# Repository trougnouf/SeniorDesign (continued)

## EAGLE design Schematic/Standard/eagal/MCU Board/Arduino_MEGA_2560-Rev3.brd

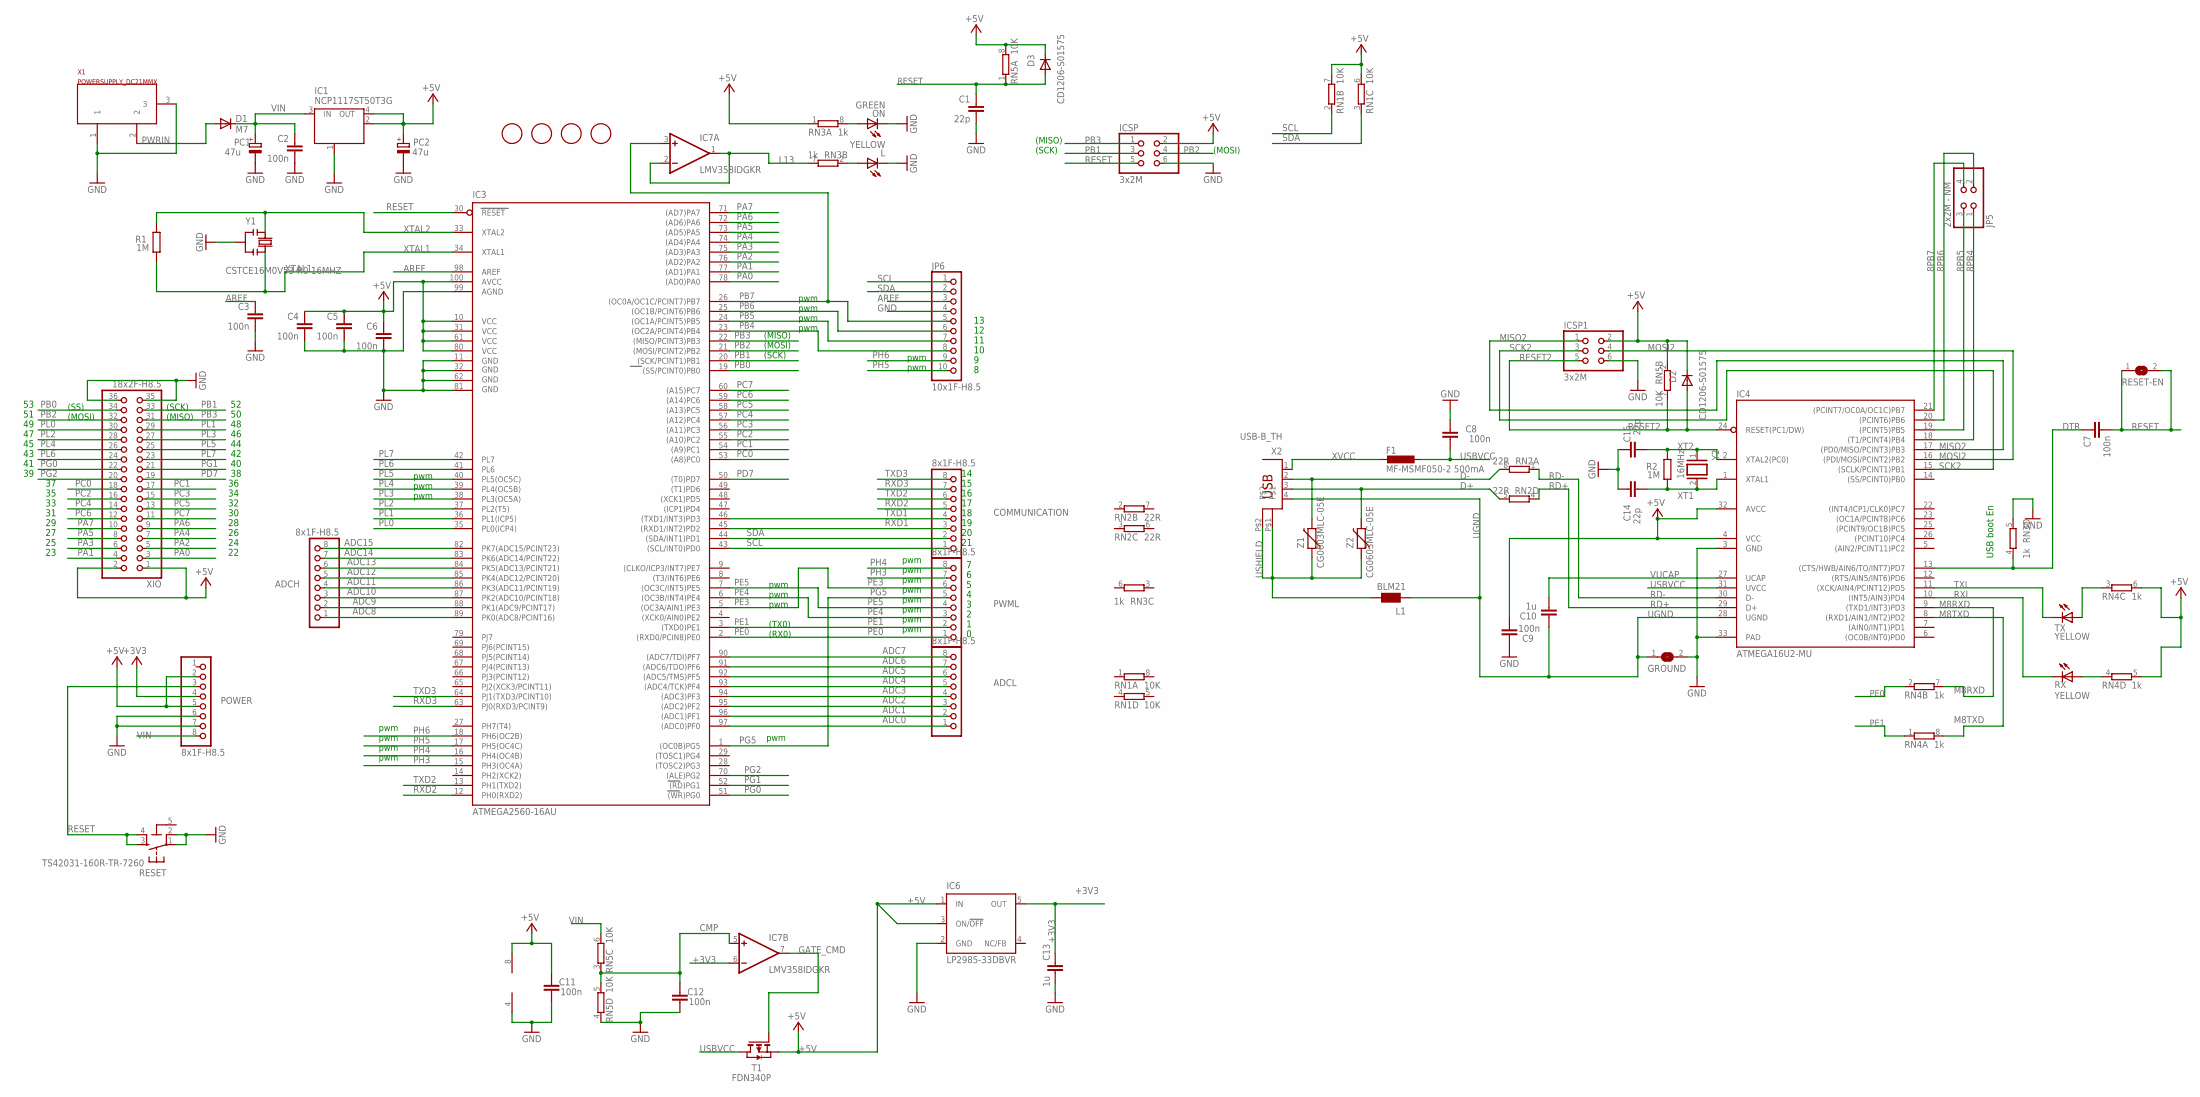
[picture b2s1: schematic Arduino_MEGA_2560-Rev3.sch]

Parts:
ADCH: 8x1F-H8.5; 1X08
ADCL: 8x1F-H8.5; 1X08
C1, C14, C15: 22p; C0603-ROUND
C2, C3, C4, C5, C6, C7, C8, C9, C11, C12: 100n; C0603-ROUND
C10, C13: 1u; C0603-ROUND
COMMUNICATION: 8x1F-H8.5; 1X08
D1: M7; SMB
D2, D3: CD1206-S01575; MINIMELF
F1: MF-MSMF050-2 500mA; L1812
FD1, FD2, FD3, FD4: FIDUCIALMOUNT; FIDUCIA-MOUNT
GROUND: SJ
IC1: NCP1117ST50T3G; SOT223
IC3: ATMEGA2560-16AU; TQFP100
IC4: ATMEGA16U2-MU; MLF32
IC6: LP2985-33DBVR; SOT23-DBV
IC7: LMV358IDGKR; MSOP08
ICSP, ICSP1: 3x2M; 2X03
JP5: 2x2M - NM; 2X02
JP6: 10x1F-H8.5; 1X10
L: YELLOW; CHIP-LED0805
L1: BLM21; 0805
ON: GREEN; CHIP-LED0805
PC1, PC2: 47u; PANASONIC_D
POWER: 8x1F-H8.5; 1X08
PWML: 8x1F-H8.5; 1X08
R1, R2: 1M; R0603-ROUND
RESET: TS42031-160R-TR-7260; TS42
RESET-EN: SJ
RN1, RN5: 10K; CAT16
RN2: 22R; CAY16
RN3, RN4: 1k; CAY16
RX: YELLOW; CHIP-LED0805
T1: FDN340P; SOT-23
TX: YELLOW; CHIP-LED0805
X1: POWERSUPPLY_DC21MMX; POWERSUPPLY_DC-21MM
X2: USB-B_TH; PN61729
XIO: 18x2F-H8.5; 2X18
Y1: CSTCE16M0V53-R0 16MHZ; RESONATOR
Y2: 16MHz; QS
Z1, Z2: CG0603MLC-05E; CT/CN0603

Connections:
5-GND: RESET.5 (5-GND)
8PB4: IC4.18 ((T1/PCINT4)PB4), JP5.1
8PB5: IC4.19 ((PCINT5)PB5), JP5.3
8PB6: IC4.20 ((PCINT6)PB6), JP5.2
8PB7: IC4.21 ((PCINT7/OC0A/OC1C)PB7), JP5.4
+3V3: C13.2, IC6.5 (OUT), IC7.6 (-IN), POWER.4
+5V: C4.1, C5.1, C6.1, C9.1, C11.2, D2.C, D3.C, IC1.2 (OUT), IC1.4 (OUT), IC3.10 (VCC), IC3.31 (VCC1), IC3.61 (VCC2), IC3.80 (VCC3), IC3.100 (AVCC), IC4.4 (VCC), IC4.32 (AVCC), IC6.1 (IN), IC6.3 (ON/!OFF), IC7.8 (V+), ICSP.2, ICSP1.2, PC2.+, POWER.2, POWER.5, RN1.6 (2), RN1.7 (2), RN3.1, RN4.5 (2), RN4.6 (2), RN5.2 (1), RN5.8 (2), T1.2 (S), XIO.1, XIO.2
ADC0: ADCL.1, IC3.97 ((ADC0)PF0)
ADC1: ADCL.2, IC3.96 ((ADC1)PF1)
ADC2: ADCL.3, IC3.95 ((ADC2)PF2)
ADC3: ADCL.4, IC3.94 ((ADC3)PF3)
ADC4: ADCL.5, IC3.93 ((ADC4/TCK)PF4)
ADC5: ADCL.6, IC3.92 ((ADC5/TMS)PF5)
ADC6: ADCL.7, IC3.91 ((ADC6/TDO)PF6)
ADC7: ADCL.8, IC3.90 ((ADC7/TDI)PF7)
ADC8: ADCH.1, IC3.89 (PK0(ADC8/PCINT16))
ADC9: ADCH.2, IC3.88 (PK1(ADC9/PCINT17))
ADC10: ADCH.3, IC3.87 (PK2(ADC10/PCINT18))
ADC11: ADCH.4, IC3.86 (PK3(ADC11/PCINT19))
ADC12: ADCH.5, IC3.85 (PK4(ADC12/PCINT20))
ADC13: ADCH.6, IC3.84 (PK5(ADC13/PCINT21))
ADC14: ADCH.7, IC3.83 (PK6(ADC14/PCINT22))
ADC15: ADCH.8, IC3.82 (PK7(ADC15/PCINT23))
AREF: C3.1, IC3.98 (AREF), JP6.3
CMP: C12.2, IC7.5 (+IN), RN5.3 (1), RN5.5 (2)
D+: RN2.5 (2), X2.3, Z2.2
D-: RN2.8 (2), X2.2, Z1.2
DTR: C7.1, IC4.13 ((CTS/HWB/AIN6/TO/INT7)PD7), RN3.4 (1)
GATE_CMD: IC7.7 (OUT), T1.3 (G)
GND: C1.2, C2.2, C3.2, C4.2, C5.2, C6.2, C8.2, C9.2, C11.1, C12.1, C13.1, C14.2, C15.2, GROUND.2, IC1.1 (GND/ADJ), IC3.11 (GND), IC3.32 (GND1), IC3.62 (GND2), IC3.81 (GND3), IC3.99 (AGND), IC4.3 (GND), IC4.33 (PAD), IC6.2 (GND), IC7.4 (V-), ICSP.6, ICSP1.6, JP6.4, L.C, ON.C, PC1.-, PC2.-, POWER.6, POWER.7, RESET.1, RESET.2, RN3.5 (2), RN5.4 (1), X1.1, X1.3, XIO.35, XIO.36, Y1.2
L13: IC7.1 (OUT), IC7.2 (-IN), RN3.7 (2)
M8RXD: IC4.9 ((TXD1/INT3)PD3), RN4.7 (2)
M8TXD: IC4.8 ((RXD1/AIN1/INT2)PD2), RN4.8 (2)
MISO2: IC4.17 ((PD0/MISO/PCINT3)PB3), ICSP1.1
MOSI2: IC4.16 ((PDI/MOSI/PCINT2)PB2), ICSP1.4
unnamed: L.A, RN3.2 (1)
unnamed: ON.A, RN3.8 (2)
unnamed: RN4.4 (1), RX.A
unnamed: RN4.3 (1), TX.A
PA0: IC3.78 ((AD0)PA0), XIO.3
PA1: IC3.77 ((AD1)PA1), XIO.4
PA2: IC3.76 ((AD2)PA2), XIO.5
PA3: IC3.75 ((AD3)PA3), XIO.6
PA4: IC3.74 ((AD4)PA4), XIO.7
PA5: IC3.73 ((AD5)PA5), XIO.8
PA6: IC3.72 ((AD6)PA6), XIO.9
PA7: IC3.71 ((AD7)PA7), XIO.10
PB0: IC3.19 ((SS/PCINT0)PB0), XIO.34
PB1: IC3.20 ((SCK/PCINT1)PB1), ICSP.3, XIO.33
PB2: IC3.21 ((MOSI/PCINT2)PB2), ICSP.4, XIO.32
PB3: IC3.22 ((MISO/PCINT3)PB3), ICSP.1, XIO.31
PB4: IC3.23 ((OC2A/PCINT4)PB4), JP6.8
PB5: IC3.24 ((OC1A/PCINT5)PB5), JP6.7
PB6: IC3.25 ((OC1B/PCINT6)PB6), JP6.6
PB7: IC3.26 ((OC0A/OC1C/PCINT7)PB7), IC7.3 (+IN), JP6.5
PC0: IC3.53 ((A8)PC0), XIO.18
PC1: IC3.54 ((A9)PC1), XIO.17
PC2: IC3.55 ((A10)PC2), XIO.16
PC3: IC3.56 ((A11)PC3), XIO.15
PC4: IC3.57 ((A12)PC4), XIO.14
PC5: IC3.58 ((A13)PC5), XIO.13
PC6: IC3.59 ((A14)PC6), XIO.12
PC7: IC3.60 ((A15)PC7), XIO.11
PD7: IC3.50 ((T0)PD7), XIO.19
PE0: IC3.2 ((RXD0/PCIN8)PE0), PWML.1, RN4.2 (1)
PE1: IC3.3 ((TXD0)PE1), PWML.2, RN4.1
PE3: IC3.5 ((OC3A/AIN1)PE3), PWML.6
PE4: IC3.6 ((OC3B/INT4)PE4), PWML.3
PE5: IC3.7 ((OC3C/INT5)PE5), PWML.4
PG0: IC3.51 ((WR)PG0), XIO.22
PG1: IC3.52 ((RD)PG1), XIO.21
PG2: IC3.70 ((ALE)PG2), XIO.20
PG5: IC3.1 ((OC0B)PG5), PWML.5
PH3: IC3.15 (PH3(OC4A)), PWML.7
PH4: IC3.16 (PH4(OC4B)), PWML.8
PH5: IC3.17 (PH5(OC4C)), JP6.10
PH6: IC3.18 (PH6(OC2B)), JP6.9
PL0: IC3.35 (PL0(ICP4)), XIO.30
PL1: IC3.36 (PL1(ICP5)), XIO.29
PL2: IC3.37 (PL2(T5)), XIO.28
PL3: IC3.38 (PL3(OC5A)), XIO.27
PL4: IC3.39 (PL4(OC5B)), XIO.26
PL5: IC3.40 (PL5(OC5C)), XIO.25
PL6: IC3.41 (PL6), XIO.24
PL7: IC3.42 (PL7), XIO.23
PWRIN: D1.A, X1.2
RD+: IC4.29 (D+), RN2.4 (1)
RD-: IC4.30 (D-), RN2.1
RESET: C1.1, C7.2, D3.A, IC3.30 (RESET), ICSP.5, POWER.3, RESET.3, RESET.4, RESET-EN.1, RESET-EN.2, RN5.1
RESET2: D2.A, IC4.24 (RESET(PC1/DW)), ICSP1.5, RN5.7 (2)
RXD1: COMMUNICATION.3, IC3.45 ((RXD1/INT2)PD2)
RXD2: COMMUNICATION.5, IC3.12 (PH0(RXD2))
RXD3: COMMUNICATION.7, IC3.63 (PJ0(RXD3/PCINT9))
RXL: IC4.10 ((INT5/AIN3)PD4), RX.C
SCK2: IC4.15 ((SCLK/PCINT1)PB1), ICSP1.3
SCL: COMMUNICATION.1, IC3.43 ((SCL/INT0)PD0), JP6.1, RN1.2 (1)
SDA: COMMUNICATION.2, IC3.44 ((SDA/INT1)PD1), JP6.2, RN1.3 (1)
TXD1: COMMUNICATION.4, IC3.46 ((TXD1/INT3)PD3)
TXD2: COMMUNICATION.6, IC3.13 (PH1(TXD2))
TXD3: COMMUNICATION.8, IC3.64 (PJ1(TXD3/PCINT10))
TXL: IC4.11 ((XCK/AIN4/PCINT12)PD5), TX.C
UGND: C10.2, GROUND.1, IC4.28 (UGND), L1.1, X2.4
USBVCC: C8.1, F1.1, IC4.31 (UVCC), T1.1 (D)
USHIELD: L1.2, X2.P$1, X2.P$2, Z1.1, Z2.1
VIN: C2.1, D1.C, IC1.3 (IN), PC1.+, POWER.8, RN5.6 (2)
VUCAP: C10.1, IC4.27 (UCAP)
XT1: C14.1, IC4.1 (XTAL1), R2.1, Y2.2
XT2: C15.1, IC4.2 (XTAL2(PC0)), R2.2, Y2.1
XTAL1: IC3.34 (XTAL1), R1.1, Y1.3
XTAL2: IC3.33 (XTAL2), R1.2, Y1.1
XVCC: F1.2, X2.1

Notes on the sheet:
(SCK)
(MISO)
(MOSI)
pwm
(TX0)
(RX0)
(SS)
USB boot En

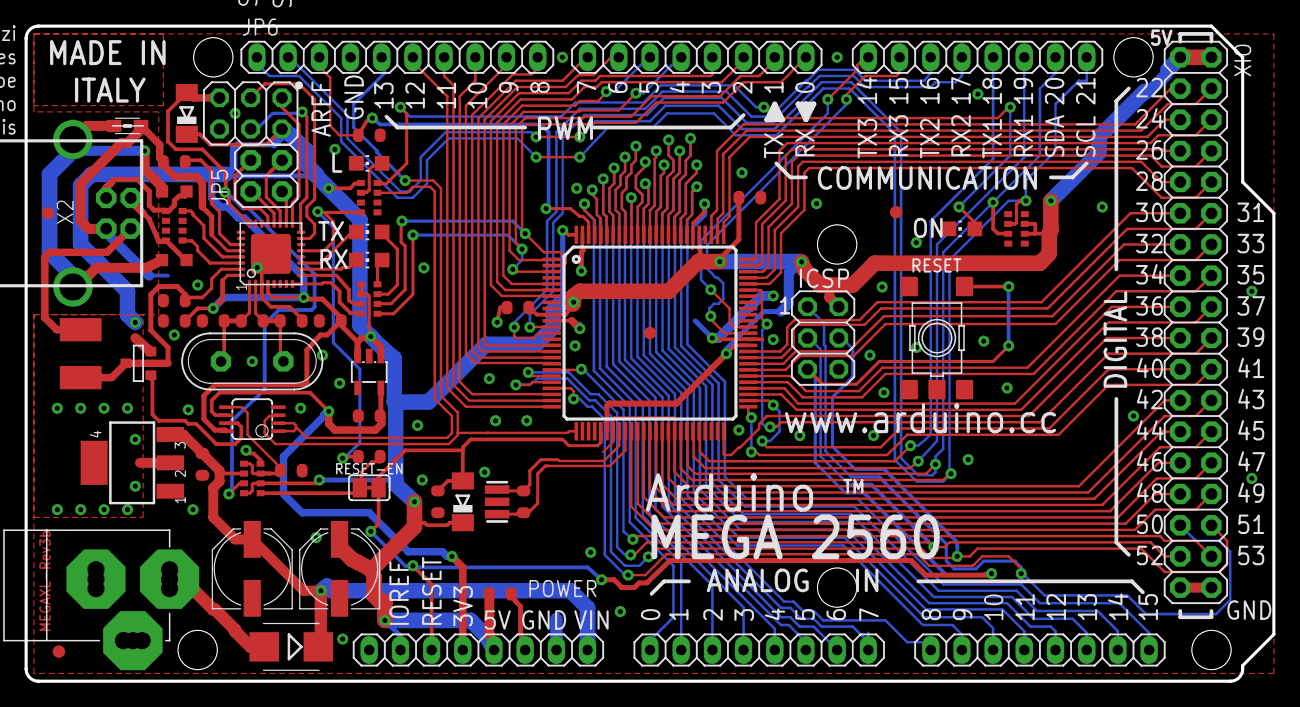
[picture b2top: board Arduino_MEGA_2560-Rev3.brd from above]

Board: 2 copper layers, 101.6 x 53.3 mm, 62 parts (1 on the bottom side), 110 nets.

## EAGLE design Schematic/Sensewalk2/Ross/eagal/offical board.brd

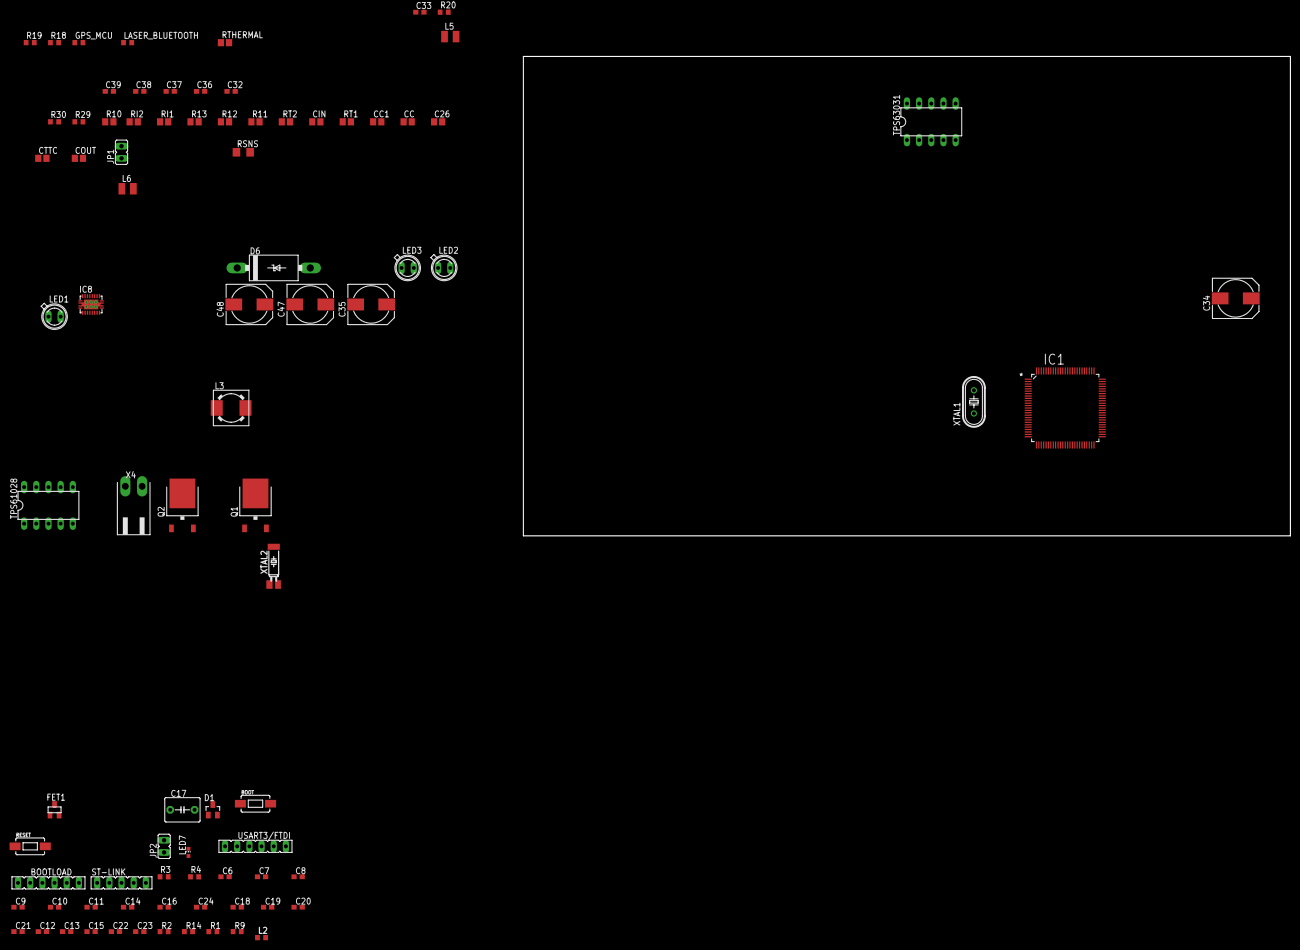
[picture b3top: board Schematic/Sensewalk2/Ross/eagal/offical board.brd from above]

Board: 2 copper layers, 160.0 x 100.0 mm, 85 parts (0 on the bottom side), 49 nets, no tracks yet.

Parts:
BOOT: SWITCH-MOMENTARY-2-SMD-1101NE; TACTILE-SWITCH-1101NE
BOOTLOAD: FE06
C6, C7, C8, C9, C10, C11, C14, C16, C24: 100nF; C0603
C12, C13, C15: 1uF; C0603
C17: 0.22F; C5B5
C18, C19: 6.8pF; C0603
C20: 22pF; C0603
C21: 22pf; C0603
C22, C23: 2u2; C0603
C26: 0.1uF; C0805
C32: 2.2uF; C0603
C33: C0603
C34, C47, C48: 347uF; 150CLZ-0810
C35: 150CLZ-0810
C36, C37, C38, C39: 10uF; C0603
CC, CC1: 0.1uF; C0805
CIN: 10uF; C0805
COUT: 10uF; C0805
CTTC: 0.1uF; C0805
D1: BAT54; SOT23
D6: MMBZ18VALT1; C4111-15
FET1: DMP2160UW; SUPER-SOT3
GPS_MCU: R0603
IC1: STM32F746VGT6; QFP50P1600X1600X160-100N
IC8: BQ24123; QFN20_3,5X4,5
JP1, JP2: JP1
L2: RCL_L0603
L3: 10uH; DR73
L5: L2825P
L6: 1.5uH; L2825P
LASER_BLUETOOTH: R0603
LED1, LED2, LED3: SFH482
LED7: CHIP-LED0603
Q1, Q2: FDD4141TO252; TO252
R1, R9, R14: 10K; R0603
R2: 47R; R0603
R3: 100R; R0603
R4: 270R; R0603
R10: 10k; R0805
R11, R12, R13: 1.5k; R0805
R18, R19, R20: R0603
R29, R30: 100k; R0603
RESET: SWITCH-MOMENTARY-2-SMD-1101NE; TACTILE-SWITCH-1101NE
RI1, RI2: 7.5k; R0805
RSNS: 0.1; R1206
RT1: 9.31k; R0805
RT2: 442k; R0805
RTHERMAL: R0805
ST-LINK: FE05-1
TPS61028, TPS63031: DIL10
USART3/FTDI: FE06
X4: 90-2
XTAL1: 8MHz; HC49U-V
XTAL2: 32768Hz; CRYSTAL_TC26H_3_REPAIR_SMD_SMALL_PITCH

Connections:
+5V: BOOTLOAD.3, C32.1, C34.+, C38.1, C39.1, C47.+, C48.+, GPS_MCU.2, JP2.1, LASER_BLUETOOTH.2, Q1.1, Q1.3, Q2.1, Q2.3, R18.2, R29.2, R30.2, TPS61028.2, TPS63031.1, TPS63031.10, USART3/FTDI.3
AGND: C32.2, C33.2, C34.-, C35.-, C36.2, C37.2, C38.2, C39.2, C47.-, C48.-, GPS_MCU.1, LASER_BLUETOOTH.1, R20.1, R29.1, R30.1, TPS61028.5, TPS61028.8, TPS61028.10, TPS63031.3, TPS63031.9
BOOT0: BOOT.P$1, FET1.3, IC1.94, R1.2
GND: BOOTLOAD.1, C6.2, C7.2, C8.2, C9.2, C10.2, C11.2, C12.2, C13.2, C14.2, C15.2, C16.2, C17.2, C18.2, C19.2, C20.2, C21.2, C22.2, C23.2, C24.2, C26.2, CC.2, CC1.2, CIN.2, COUT.2, CTTC.2, D6.A, IC1.10, IC1.19, IC1.26, IC1.49, IC1.74, IC1.99, IC8.10, IC8.16, IC8.17, IC8.18, R1.1, R4.1, R14.1, RESET.P$1, RI1.2, RI2.2, RT2.1, RTHERMAL.2, ST-LINK.3, USART3/FTDI.1, X4.2, XTAL2.GND
unnamed: Q1.2, Q2.2
unnamed: D6.C, IC8.1, IC8.20, L3.1
unnamed: CC.1, COUT.1, IC8.15, L3.2, RSNS.1
unnamed: IC8.8, RI1.1
unnamed: IC8.9, RI2.1
unnamed: IC8.12, RT1.1, RT2.2, RTHERMAL.1
unnamed: CC1.1, IC8.11, RT1.2
unnamed: LED3.A, R13.1
unnamed: LED2.A, R12.1
unnamed: LED1.A, R11.1
unnamed: IC8.2, LED1.K
unnamed: IC8.19, LED2.K
unnamed: IC8.5, LED3.K
unnamed: CTTC.1, IC8.7
unnamed: IC8.13, R10.1
unnamed: C26.1, CIN.1, IC8.3, IC8.4, IC8.6, JP1.2, R10.2, R11.2, R12.2, R13.2
unnamed: D1.3, R3.2
unnamed: R18.1, TPS61028.4
unnamed: R19.2, TPS61028.1, TPS61028.6
unnamed: L5.1, TPS61028.9
unnamed: C33.1, C35.+, C36.1, IC8.14, L5.2, R19.1, R20.2, RSNS.2, TPS61028.7, TPS63031.5, X4.1
unnamed: L6.2, TPS63031.2
unnamed: L6.1, TPS63031.4
unnamed: C37.1, TPS63031.6, TPS63031.7, TPS63031.8
unnamed: LED7.C, R4.2
NRST: C24.1, IC1.14, R9.1, RESET.P$2, ST-LINK.5
PA9: BOOTLOAD.5, IC1.68
PA10: BOOTLOAD.4, IC1.69
PA13: IC1.72, ST-LINK.4
PA14: IC1.76, ST-LINK.2
PB2: IC1.36, R14.2
PC13: IC1.7, LED7.A
PC14: C18.1, IC1.8, XTAL2.1
PC15: C19.1, IC1.9, XTAL2.2
PD1: FET1.1, IC1.82
PD8: IC1.55, USART3/FTDI.5
PD9: IC1.56, USART3/FTDI.4
PH0: C21.1, IC1.12, XTAL1.2
PH1: C20.1, IC1.13, XTAL1.1
VBAT: C17.1, IC1.6, R3.1
VCAP_1: C22.1, IC1.48
VCAP_2: C23.1, IC1.73
VCC: BOOT.P$2, C6.1, C7.1, C8.1, C9.1, C10.1, C11.1, C12.1, D1.1, FET1.2, IC1.11, IC1.27, IC1.50, IC1.75, IC1.100, L2.1, R9.2, ST-LINK.1
VDDA: C13.1, C14.1, IC1.21, L2.2, R2.2
VREF: C15.1, C16.1, IC1.20, R2.1

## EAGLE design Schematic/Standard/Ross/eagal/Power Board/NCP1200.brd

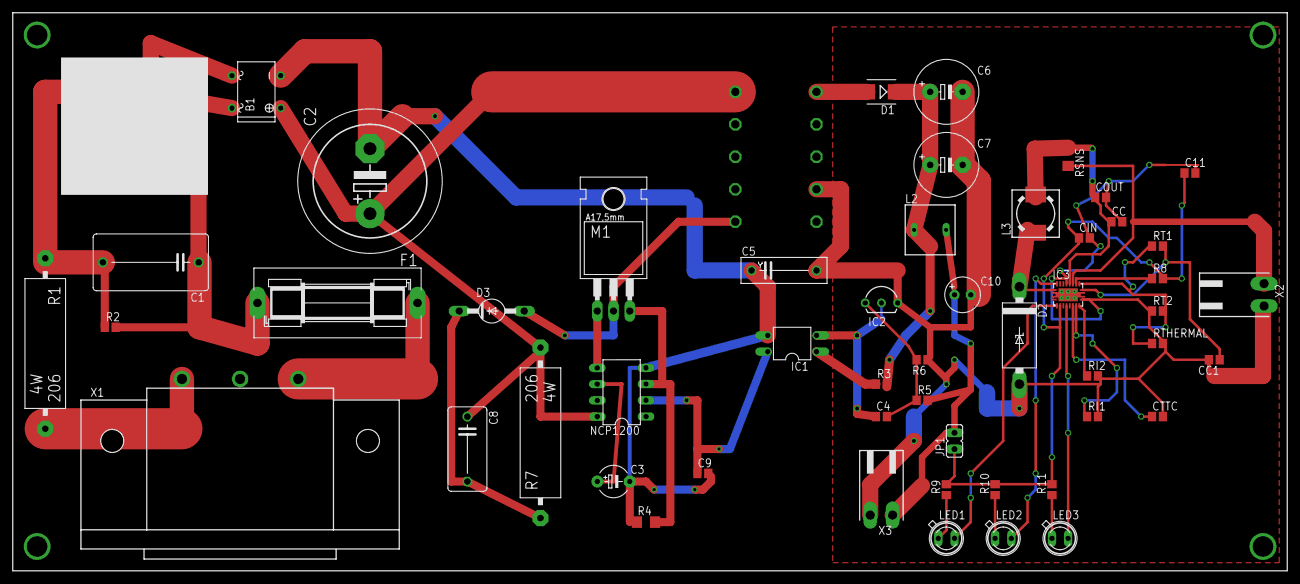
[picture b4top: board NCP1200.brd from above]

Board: 2 copper layers, 199.4 x 87.3 mm, 54 parts (1 on the bottom side), 37 nets.

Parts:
B1: B-DIL
C1: 1uF; C150-091X182
C2: 47uF; EB22,5D
C3: 22uF; E5-5
C4: 100nF; C0805
C5: 2.2nF; YC10B4
C6, C7: 470uF; E5-10,5
C8: 10nF; C102-064X133
C9: 1nF; C0805
C10: 100uF; E2,5-6
C11: 0.1uF; C0805
CC, CC1: 0.1uF; C0805
CIN: 10uF; C0805
COUT: 10uF; C0805
CTTC: 0.1uF; C0805
D1: MBR360T3; SMB
D2: MMBZ18VALT1; C4111-15
D3: MUR160; SGA-10
F1: SH25
IC1: PC817; DIL04
IC2: TL431; LP_O-PBCY-W3
IC3: BQ24123; QFN20_3,5X4,5
JP1: JP1
L2: 22uH; SD8
L3: 10uH; DR73
LED1, LED2, LED3: SFH482
M1: NDF03N60ZG; TO220
NCP1200: DIL08
R1: 10; KH206-8
R2: 1Meg; R0805
R3: 560; R0805
R4: 1.8; R1206
R5: 3.9k; R0805
R6: 1k; R0805
R7: 22k; KH206-8
R8: 10k; R0805
R9, R10, R11: 1.5k; R0805
RI1, RI2: 7.5k; R0805
RSNS: 0.1; R1206
RT1: 9.31k; R0805
RT2: 442k; R0805
RTHERMAL: R0805
U$1: RENCO1
U$2: L1CHO5; L1CHO
X1: 6ESRM-P
X2, X3: 90-2

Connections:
GND: C5.2, C6.-, C7.-, C10.-, C11.2, CC.2, CC1.2, CIN.2, COUT.2, CTTC.2, D2.A, IC2.3, IC3.10, IC3.16, IC3.17, IC3.18, R6.1, RI1.2, RI2.2, RT2.1, RTHERMAL.2, U$1.P7, X2.2, X3.2
unnamed: D2.C, IC3.1, IC3.20, L3.1
unnamed: C1.2, R1.1, R2.1, U$2.P3
unnamed: CC.1, COUT.1, IC3.15, L3.2, RSNS.1
unnamed: B1.AC1, U$2.P2
unnamed: B1.AC2, U$2.P4
unnamed: IC3.8, RI1.1
unnamed: B1.+, C2.+, C8.1, NCP1200.8, R7.2, U$1.P1
unnamed: C9.1, IC1.4, NCP1200.2
unnamed: M1.1, NCP1200.5
unnamed: M1.3, NCP1200.3, R4.2
unnamed: C3.+, NCP1200.6
unnamed: C11.1, CIN.1, IC3.3, IC3.4, IC3.6, JP1.1, R8.2, R9.2, R10.2, R11.2
unnamed: D1.A, U$1.P10
unnamed: C8.2, D3.C, R7.1
unnamed: D3.A, M1.2, U$1.P5
unnamed: C6.+, C7.+, D1.C, L2.1, R3.2
unnamed: IC1.1, R3.1
unnamed: IC3.9, RI2.1
unnamed: C4.2, IC2.1, R5.1, R6.2
unnamed: C4.1, IC1.2, IC2.2
unnamed: IC3.12, RT1.1, RT2.2, RTHERMAL.1
unnamed: CC1.1, IC3.11, RT1.2
unnamed: LED3.A, R11.1
unnamed: LED2.A, R10.1
unnamed: LED1.A, R9.1
unnamed: IC3.2, LED1.K
unnamed: IC3.19, LED2.K
unnamed: IC3.5, LED3.K
unnamed: CTTC.1, IC3.7
unnamed: IC3.13, R8.1
unnamed: C1.1, F1.2, R2.2, U$2.P1
unnamed: R1.2, X1.1
unnamed: IC3.14, RSNS.2, X2.1
unnamed: F1.1, X1.3
unnamed: C10.+, JP1.2, L2.2, R5.2, X3.1
PE: B1.-, C2.-, C3.-, C5.1, C9.2, IC1.3, NCP1200.4, R4.1

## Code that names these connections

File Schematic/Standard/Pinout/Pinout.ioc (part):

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Mcu.Name=STM32F746Z(E-G)Tx
Mcu.Package=LQFP144
Mcu.UserName=STM32F746ZGTx
PA0/WKUP.GPIOParameters=GPIO_Label
PA0/WKUP.GPIO_Label=UART_TX_Laser
PA0/WKUP.Mode=Asynchronous
PA0/WKUP.Signal=UART4_TX
PA1.GPIOParameters=GPIO_Label
PA1.GPIO_Label=UART_RX_Laser
PA1.Mode=Asynchronous
PA1.Signal=UART4_RX
PA10.Mode=Slave_8_bits_External_Synchro
PA10.Signal=DCMI_D1
PA13.Mode=Trace-Asynchronous_SW
PA13.Signal=SYS_JTMS-SWDIO
PA14.Mode=Trace-Asynchronous_SW
PA14.Signal=SYS_JTCK-SWCLK
PA15.GPIOParameters=GPIO_Label
PA15.GPIO_Label=SPI1_NSS_Compass
PA15.Mode=NSS_Signal_Hard_Input
PA15.Signal=SPI1_NSS
PA2.GPIOParameters=GPIO_Label
PA2.GPIO_Label=ADC_IN2_Mic
PA2.Signal=ADCx_IN2
PA4.Mode=Slave_8_bits_External_Synchro
PA4.Signal=DCMI_HSYNC
PA5.GPIOParameters=GPIO_Label
PA5.GPIO_Label=SPI_CLK_Compass
PA5.Mode=Full_Duplex_Master
PA5.Signal=SPI1_SCK
PA6.Mode=Slave_8_bits_External_Synchro
PA6.Signal=DCMI_PIXCLK
PA7.GPIOParameters=GPIO_Label
PA7.GPIO_Label=SPI_MOSI_Compass
PA7.Mode=Full_Duplex_Master
PA7.Signal=SPI1_MOSI
PA9.GPIOParameters=GPIO_Label
PA9.GPIO_Label=USART1_TX_Debug
PA9.Mode=Asynchronous
PA9.Signal=USART1_TX
PB10.GPIOParameters=GPIO_Label
PB10.GPIO_Label=I2C2_SCL_Codec
PB10.Mode=I2C
PB10.Signal=I2C2_SCL
PB11.GPIOParameters=GPIO_Label
PB11.GPIO_Label=I2C2_SDA_Codec
PB11.Mode=I2C
PB11.Signal=I2C2_SDA
PB12.GPIOParameters=GPIO_Label
PB12.GPIO_Label=DATA_REQ_Codec
PB12.Signal=GPIO_Input
PB13.Mode=TX_Only_Simplex_Unidirect_Master
PB13.Signal=SPI2_SCK
PB14.GPIOParameters=GPIO_Label
PB14.GPIO_Label=RST_Codec
PB14.Signal=GPIO_Output
PB2.Mode=Single Bank 1
PB2.Signal=QUADSPI_CLK
PB3.Mode=Trace-Asynchronous_SW
PB3.Signal=SYS_JTDO-SWO
PB4.GPIOParameters=GPIO_Label
PB4.GPIO_Label=SPI_MISO_Compass
PB4.Mode=Full_Duplex_Master
PB4.Signal=SPI1_MISO
PB6.Mode=Single Bank 1
PB6.Signal=QUADSPI_BK1_NCS
PB7.GPIOParameters=GPIO_Label
PB7.GPIO_Label=USART1_RX_Debug
PB7.Mode=Asynchronous
PB7.Signal=USART1_RX
PC0.Signal=FMC_SDNWE
PC1.Mode=TX_Only_Simplex_Unidirect_Master
PC1.Signal=SPI2_MOSI
PC12.Mode=SD_1_bit
PC12.Signal=SDMMC1_CK
PC13.GPIOParameters=GPIO_Label
PC13.GPIO_Label=RET_Camera
PC13.Signal=GPIO_Output
PC2.Mode=SdramChipSelect1_1
PC2.Signal=FMC_SDNE0
PC3.Mode=SdramChipSelect1_1
PC3.Signal=FMC_SDCKE0
PC4.GPIOParameters=GPIO_Label
PC4.GPIO_Label=INT_Compass
PC4.Signal=GPIO_Output
PC5.GPIOParameters=GPIO_Label
PC5.GPIO_Label=TRIG_Compass
PC5.Signal=GPIO_Output
PC6.Mode=Slave_8_bits_External_Synchro
PC6.Signal=DCMI_D0
PC7.GPIOParameters=GPIO_Label
PC7.GPIO_Label=USART6_RX_BT
PC7.Mode=Asynchronous
PC7.Signal=USART6_RX
PC8.Mode=SD_1_bit
PC8.Signal=SDMMC1_D0
PD0.Signal=FMC_D2_DA2
PD1.Signal=FMC_D3_DA3
PD10.Signal=FMC_D15_DA15
PD13.Mode=Single Bank 1
PD13.Signal=QUADSPI_BK1_IO3
PD14.Signal=FMC_D0_DA0
PD15.Signal=FMC_D1_DA1
PD2.Mode=SD_1_bit
PD2.Signal=SDMMC1_CMD
PD3.GPIOParameters=GPIO_Label
PD3.GPIO_Label=DCMI_D5_Camera
PD3.Mode=Slave_8_bits_External_Synchro
PD3.Signal=DCMI_D5
PD8.Signal=FMC_D13_DA13
PD9.Signal=FMC_D14_DA14
PE0.Signal=FMC_NBL0
PE1.Signal=FMC_NBL1
PE10.Signal=FMC_D7_DA7
PE11.Signal=FMC_D8_DA8
PE12.Signal=FMC_D9_DA9
PE13.Signal=FMC_D10_DA10
PE14.Signal=FMC_D11_DA11
PE15.Signal=FMC_D12_DA12
PE2.Mode=Single Bank 1
PE2.Signal=QUADSPI_BK1_IO2
PE3.GPIOParameters=GPIO_Label
PE3.GPIO_Label=PWDN_Camera
PE3.Signal=GPIO_Output
PE4.GPIOParameters=GPIO_Label
PE4.GPIO_Label=DCMI_D4_Camera
PE4.Mode=Slave_8_bits_External_Synchro
PE4.Signal=DCMI_D4
PE5.GPIOParameters=GPIO_Label
PE5.GPIO_Label=DCMI_D6_Camera
PE5.Mode=Slave_8_bits_External_Synchro
PE5.Signal=DCMI_D6
PE6.GPIOParameters=GPIO_Label
PE6.GPIO_Label=DCMI_D7_Camera
PE6.Mode=Slave_8_bits_External_Synchro
PE6.Signal=DCMI_D7
PE7.Signal=FMC_D4_DA4
PE8.Signal=FMC_D5_DA5
PE9.Signal=FMC_D6_DA6
PF0.Signal=FMC_A0
PF1.Signal=FMC_A1
PF11.Signal=FMC_SDNRAS
PF12.Signal=FMC_A6
PF13.Signal=FMC_A7
PF14.Signal=FMC_A8
PF15.Signal=FMC_A9
PF2.Signal=FMC_A2
PF3.Signal=FMC_A3
PF4.Signal=FMC_A4
PF5.Signal=FMC_A5
PF6.GPIOParameters=GPIO_Label
PF6.GPIO_Label=UART7_RX_GPS
PF6.Mode=Asynchronous
PF6.Signal=UART7_RX
PF7.GPIOParameters=GPIO_Label
PF7.GPIO_Label=UART7_TX_GPS
PF7.Mode=Asynchronous
PF7.Signal=UART7_TX
PF8.Mode=Single Bank 1
PF8.Signal=QUADSPI_BK1_IO0
PF9.Mode=Single Bank 1
PF9.Signal=QUADSPI_BK1_IO1
PG0.Signal=FMC_A10
PG1.Signal=FMC_A11
PG10.GPIOParameters=GPIO_Label
PG10.GPIO_Label=DCMI_D2_Camera
PG10.Mode=Slave_8_bits_External_Synchro
PG10.Signal=DCMI_D2
PG11.GPIOParameters=GPIO_Label
PG11.GPIO_Label=DCMI_D3_Camera
PG11.Mode=Slave_8_bits_External_Synchro
PG11.Signal=DCMI_D3
PG12.GPIOParameters=GPIO_Label
PG12.GPIO_Label=USART6_RTS_BT
PG12.Mode=CTS_RTS
PG12.Signal=USART6_RTS
PG13.GPIOParameters=GPIO_Label
PG13.GPIO_Label=USART6_CTS_BT
PG13.Mode=CTS_RTS
PG13.Signal=USART6_CTS
PG14.GPIOParameters=GPIO_Label
PG14.GPIO_Label=USART6_TX_BT
PG14.Mode=Asynchronous
PG14.Signal=USART6_TX
PG15.Signal=FMC_SDNCAS
PG4.Signal=FMC_A14_BA0
PG5.Signal=FMC_A15_BA1
PG8.Signal=FMC_SDCLK
PG9.Mode=Slave_8_bits_External_Synchro
PG9.Signal=DCMI_VSYNC
RCC.HSE_VALUE=25000000
board=Pinout
boardIOC=true

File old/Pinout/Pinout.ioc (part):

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Mcu.Name=STM32F746Z(E-G)Tx
Mcu.Package=LQFP144
Mcu.UserName=STM32F746ZGTx
PA0/WKUP.GPIOParameters=GPIO_Label
PA0/WKUP.GPIO_Label=UART_TX_Laser
PA0/WKUP.Mode=Asynchronous
PA0/WKUP.Signal=UART4_TX
PA1.GPIOParameters=GPIO_Label
PA1.GPIO_Label=UART_RX_Laser
PA1.Mode=Asynchronous
PA1.Signal=UART4_RX
PA10.GPIOParameters=GPIO_Label
PA10.GPIO_Label=UART_RX_BT
PA10.Mode=Asynchronous
PA10.Signal=USART1_RX
PA11.GPIOParameters=GPIO_Label
PA11.GPIO_Label=UART_CTS_BT
PA11.Mode=CTS_RTS
PA11.Signal=USART1_CTS
PA12.GPIOParameters=GPIO_Label
PA12.GPIO_Label=UART_RTS_BT
PA12.Mode=CTS_RTS
PA12.Signal=USART1_RTS
PA13.Mode=Trace-Asynchronous_SW
PA13.Signal=SYS_JTMS-SWDIO
PA14.Mode=Trace-Asynchronous_SW
PA14.Signal=SYS_JTCK-SWCLK
PA2.GPIOParameters=GPIO_Label
PA2.GPIO_Label=ADC_IN2_Mic
PA2.Signal=ADCx_IN2
PA3.GPIOParameters=GPIO_Label
PA3.GPIO_Label=UART_RX_GPS
PA3.Mode=Asynchronous
PA3.Signal=USART2_RX
PA4.Mode=Slave_8_bits_External_Synchro
PA4.Signal=DCMI_HSYNC
PA5.GPIOParameters=GPIO_Label
PA5.GPIO_Label=SPI_CLK_Compass
PA5.Mode=Full_Duplex_Master
PA5.Signal=SPI1_SCK
PA6.Mode=Slave_8_bits_External_Synchro
PA6.Signal=DCMI_PIXCLK
PA7.GPIOParameters=GPIO_Label
PA7.GPIO_Label=SPI_MOSI_Compass
PA7.Mode=Full_Duplex_Master
PA7.Signal=SPI1_MOSI
PA9.GPIOParameters=GPIO_Label
PA9.GPIO_Label=UART_TX_BT
PA9.Mode=Asynchronous
PA9.Signal=USART1_TX
PB2.Mode=Single Bank 1
PB2.Signal=QUADSPI_CLK
PB3.Mode=Trace-Asynchronous_SW
PB3.Signal=SYS_JTDO-SWO
PB4.GPIOParameters=GPIO_Label
PB4.GPIO_Label=SPI_MISO_Compass
PB4.Mode=Full_Duplex_Master
PB4.Signal=SPI1_MISO
PB6.Mode=Single Bank 1
PB6.Signal=QUADSPI_BK1_NCS
PB7.GPIOParameters=GPIO_Label
PB7.GPIO_Label=I2C_SDA_Codec
PB7.Mode=I2C
PB7.Signal=I2C1_SDA
PB8.GPIOParameters=GPIO_Label
PB8.GPIO_Label=I2C_SCL_Codec
PB8.Mode=I2C
PB8.Signal=I2C1_SCL
PC0.Signal=FMC_SDNWE
PC10.Mode=SD_4_bits_Wide_bus
PC10.Signal=SDMMC1_D2
PC11.Mode=SD_4_bits_Wide_bus
PC11.Signal=SDMMC1_D3
PC12.Mode=SD_4_bits_Wide_bus
PC12.Signal=SDMMC1_CK
PC2.Mode=SdramChipSelect1_1
PC2.Signal=FMC_SDNE0
PC3.Mode=SdramChipSelect1_1
PC3.Signal=FMC_SDCKE0
PC6.Mode=Slave_8_bits_External_Synchro
PC6.Signal=DCMI_D0
PC7.Mode=Slave_8_bits_External_Synchro
PC7.Signal=DCMI_D1
PC8.Mode=SD_4_bits_Wide_bus
PC8.Signal=SDMMC1_D0
PC9.Mode=SD_4_bits_Wide_bus
PC9.Signal=SDMMC1_D1
PD0.Signal=FMC_D2_DA2
PD1.Signal=FMC_D3_DA3
PD10.Signal=FMC_D15_DA15
PD13.Mode=Single Bank 1
PD13.Signal=QUADSPI_BK1_IO3
PD14.Signal=FMC_D0_DA0
PD15.Signal=FMC_D1_DA1
PD2.Mode=SD_4_bits_Wide_bus
PD2.Signal=SDMMC1_CMD
PD3.Mode=Slave_8_bits_External_Synchro
PD3.Signal=DCMI_D5
PD5.GPIOParameters=GPIO_Label
PD5.GPIO_Label=UART_TX_GPS
PD5.Mode=Asynchronous
PD5.Signal=USART2_TX
PD8.Signal=FMC_D13_DA13
PD9.Signal=FMC_D14_DA14
PE0.Signal=FMC_NBL0
PE1.Signal=FMC_NBL1
PE10.Signal=FMC_D7_DA7
PE11.Signal=FMC_D8_DA8
PE12.Signal=FMC_D9_DA9
PE13.Signal=FMC_D10_DA10
PE14.Signal=FMC_D11_DA11
PE15.Signal=FMC_D12_DA12
PE2.Mode=Single Bank 1
PE2.Signal=QUADSPI_BK1_IO2
PE4.Mode=Slave_8_bits_External_Synchro
PE4.Signal=DCMI_D4
PE5.Mode=Slave_8_bits_External_Synchro
PE5.Signal=DCMI_D6
PE6.Mode=Slave_8_bits_External_Synchro
PE6.Signal=DCMI_D7
PE7.Signal=FMC_D4_DA4
PE8.Signal=FMC_D5_DA5
PE9.Signal=FMC_D6_DA6
PF0.Signal=FMC_A0
PF1.Signal=FMC_A1
PF11.Signal=FMC_SDNRAS
PF12.Signal=FMC_A6
PF13.Signal=FMC_A7
PF14.Signal=FMC_A8
PF15.Signal=FMC_A9
PF2.Signal=FMC_A2
PF3.Signal=FMC_A3
PF4.Signal=FMC_A4
PF5.Signal=FMC_A5
PF6.GPIOParameters=GPIO_Label
PF6.GPIO_Label=UART_RX_Debug
PF6.Mode=Asynchronous
PF6.Signal=UART7_RX
PF7.GPIOParameters=GPIO_Label
PF7.GPIO_Label=UART_TX_Debug
PF7.Mode=Asynchronous
PF7.Signal=UART7_TX
PF8.Mode=Single Bank 1
PF8.Signal=QUADSPI_BK1_IO0
PF9.Mode=Single Bank 1
PF9.Signal=QUADSPI_BK1_IO1
PG0.Signal=FMC_A10
PG1.Signal=FMC_A11
PG10.Mode=Slave_8_bits_External_Synchro
PG10.Signal=DCMI_D2
PG11.Mode=Slave_8_bits_External_Synchro
PG11.Signal=DCMI_D3
PG15.Signal=FMC_SDNCAS
PG4.Signal=FMC_A14_BA0
PG5.Signal=FMC_A15_BA1
PG8.Signal=FMC_SDCLK
PG9.Mode=Slave_8_bits_External_Synchro
PG9.Signal=DCMI_VSYNC
RCC.HSE_VALUE=25000000
board=Pinout
boardIOC=true

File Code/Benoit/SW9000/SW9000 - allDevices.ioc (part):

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Mcu.Name=STM32L476R(C-E-G)Tx
Mcu.Package=LQFP64
Mcu.UserName=STM32L476RETx
PA0.GPIOParameters=GPIO_Label
PA0.GPIO_Label=UART4_TX_Laser
PA0.Mode=Asynchronous
PA0.Signal=UART4_TX
PA1.GPIOParameters=GPIO_Label
PA1.GPIO_Label=UART4_RX_Laser
PA1.Mode=Asynchronous
PA1.Signal=UART4_RX
PA10.Signal=GPIO_Input
PA11.Signal=GPIO_Input
PA12.Signal=GPIO_Input
PA13.Mode=Serial-Wire
PA13.Signal=SYS_JTMS-SWDIO
PA14.Mode=Serial-Wire
PA14.Signal=SYS_JTCK-SWCLK
PA15.GPIOParameters=GPIO_Label
PA15.GPIO_Label=SDMMC1_Detect
PA15.Signal=GPIO_Input
PA2.GPIOParameters=GPIO_Label
PA2.GPIO_Label=USART2_TX_PC
PA2.Mode=Asynchronous
PA2.Signal=USART2_TX
PA3.GPIOParameters=GPIO_Label
PA3.GPIO_Label=USART2_RX_PC
PA3.Mode=Asynchronous
PA3.Signal=USART2_RX
PA4.Mode=SAI_B_Master
PA4.Signal=SAI1_FS_B
PA5.GPIOParameters=GPIO_Label
PA5.GPIO_Label=SPI1_SCK_Codec
PA5.Mode=TX_Only_Simplex_Unidirect_Master
PA5.Signal=SPI1_SCK
PA6.GPIOParameters=GPIO_Label
PA6.GPIO_Label=USART3_CTS_BT
PA6.Mode=CTS_RTS
PA6.Signal=USART3_CTS
PA7.GPIOParameters=GPIO_Label
PA7.GPIO_Label=SPI1_MOSI_Codec
PA7.Mode=TX_Only_Simplex_Unidirect_Master
PA7.Signal=SPI1_MOSI
PA8.Signal=GPIO_Input
PA9.GPIOParameters=GPIO_Label
PA9.GPIO_Label=USART1_TX_GPS
PA9.Mode=Asynchronous
PA9.Signal=USART1_TX
PB0.GPIOParameters=GPIO_Label
PB0.GPIO_Label=VIBRATOR
PB0.Signal=GPIO_Output
PB1.GPIOParameters=GPIO_Label
PB1.GPIO_Label=USART3_RTS_BT
PB1.Mode=CTS_RTS
PB1.Signal=USART3_RTS
PB10.GPIOParameters=GPIO_Label
PB10.GPIO_Label=SPI2_SCK_Compass
PB10.Mode=Full_Duplex_Master
PB10.Signal=SPI2_SCK
PB11.GPIOParameters=GPIO_Label
PB11.GPIO_Label=BT_GP9
PB11.Signal=GPIO_Output
PB12.GPIOParameters=GPIO_Label
PB12.GPIO_Label=COMP_INT
PB12.Signal=GPIO_Input
PB13.GPIOParameters=GPIO_Label
PB13.GPIO_Label=INT2_Compass
PB13.Signal=GPIO_Input
PB14.GPIOParameters=GPIO_Label
PB14.GPIO_Label=RST_Codec
PB14.Signal=GPIO_Output
PB15.GPIOParameters=GPIO_Label
PB15.GPIO_Label=SPI2_MOSI_Compass
PB15.Mode=Full_Duplex_Master
PB15.Signal=SPI2_MOSI
PB2.GPIOParameters=GPIO_Label
PB2.GPIO_Label=BT_GP2
PB2.Signal=GPIO_Output
PB3.Mode=SAI_B_Master
PB3.Signal=SAI1_SCK_B
PB5.Mode=SAI_B_Master
PB5.Signal=SAI1_SD_B
PB7.GPIOParameters=GPIO_Label
PB7.GPIO_Label=USART1_RX_GPS
PB7.Mode=Asynchronous
PB7.Signal=USART1_RX
PB8.GPIOParameters=GPIO_Label
PB8.GPIO_Label=LED
PB8.Signal=GPIO_Output
PB9.GPIOParameters=GPIO_Label
PB9.GPIO_Label=COMP_CS
PB9.Signal=GPIO_Output
PC0.GPIOParameters=GPIO_Label
PC0.GPIO_Label=I2C3_SCL_Codec
PC0.Mode=I2C
PC0.Signal=I2C3_SCL
PC1.GPIOParameters=GPIO_Label
PC1.GPIO_Label=I2C3_SDA_Codec
PC1.Mode=I2C
PC1.Signal=I2C3_SDA
PC12.Mode=SD_1_bit
PC12.Signal=SDMMC1_CK
PC13.Mode=SYS-WakeUp2
PC13.Signal=SYS_WKUP2
PC14/OSC32_IN.Signal=GPIO_Input
PC15/OSC32_OUT.Signal=GPIO_Input
PC2.GPIOParameters=GPIO_Label
PC2.GPIO_Label=SPI2_MISO_Compass
PC2.Mode=Full_Duplex_Master
PC2.Signal=SPI2_MISO
PC4.GPIOParameters=GPIO_Label
PC4.GPIO_Label=USART3_TX_BT
PC4.Mode=Asynchronous
PC4.Signal=USART3_TX
PC5.GPIOParameters=GPIO_Label
PC5.GPIO_Label=USART3_RX_BT
PC5.Mode=Asynchronous
PC5.Signal=USART3_RX
PC6.GPIOParameters=GPIO_Label
PC6.GPIO_Label=Codec_DR
PC6.Signal=GPIO_Input
PC7.GPIOParameters=GPIO_Label
PC7.GPIO_Label=FIVEVOLTSEN
PC7.Signal=GPIO_Output
PC8.Mode=SD_1_bit
PC8.Signal=SDMMC1_D0
PD2.Mode=SD_1_bit
PD2.Signal=SDMMC1_CMD
PH0/OSC_IN.Signal=GPIO_Input
PH1/OSC_OUT.Signal=GPIO_Input
RCC.HSE_VALUE=8000000
RCC.SYSCLKFreq_VALUE=80000000
RCC.SYSCLKSource=RCC_SYSCLKSOURCE_PLLCLK
board=SW9000
boardIOC=true

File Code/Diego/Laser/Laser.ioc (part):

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Mcu.Name=STM32F070RBTx
Mcu.Package=LQFP64
Mcu.UserName=STM32F070RBTx
PA0.GPIOParameters=GPIO_Label
PA0.GPIO_Label=LED2-n
PA0.Signal=GPIO_Output
PA1.GPIOParameters=GPIO_Label
PA1.GPIO_Label=LED2-p
PA1.Signal=GPIO_Output
PA10.GPIOParameters=GPIO_Label
PA10.GPIO_Label=GPS_RX
PA10.Mode=Asynchronous
PA10.Signal=USART1_RX
PA2.GPIOParameters=GPIO_Label
PA2.GPIO_Label=PC_TX
PA2.Mode=Asynchronous
PA2.Signal=USART2_TX
PA3.GPIOParameters=GPIO_Label
PA3.GPIO_Label=PC_RX
PA3.Mode=Asynchronous
PA3.Signal=USART2_RX
PA4.GPIOParameters=GPIO_Label
PA4.GPIO_Label=LED1-n
PA4.Signal=GPIO_Output
PA9.GPIOParameters=GPIO_Label
PA9.GPIO_Label=GPS_TX
PA9.Mode=Asynchronous
PA9.Signal=USART1_TX
PB0.GPIOParameters=GPIO_Label
PB0.GPIO_Label=LED1-p
PB0.Signal=GPIO_Output
PC0.GPIOParameters=GPIO_Label
PC0.GPIO_Label=LED0-p
PC0.Signal=GPIO_Output
PC1.GPIOParameters=GPIO_Label
PC1.GPIO_Label=LED0-n
PC1.Signal=GPIO_Output
RCC.SYSCLKFreq_VALUE=48000000
RCC.SYSCLKSource=RCC_SYSCLKSOURCE_PLLCLK
board=NUCLEO-F070RB
boardIOC=true

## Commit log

2015-12-25 Initial commit. Datasheets and initial code w/RTOS example
2015-12-26 Added some datasheets
2015-12-26 Added STM32F7Cube firmware
2016-01-03 Added TODO list
2016-01-15 Added some documentation
2016-01-15 Uploaded datasheet for bluetooth and codec, started pinout
2016-01-16 List of passive components required for the MP3 decoder.
2016-01-21 Update TODO
2016-01-22 Added readme.txt containing useful functions/examples
2016-01-22 Add Pinout.ioc (STM32CubeMX), update Pinout.txt
2016-01-22 Update pinout
2016-01-22 Add STLink/Discovery built-in UART ports
2016-01-29 GPS data output
2016-01-30 sync, no progress
2016-01-31 Add FatFS support (SD card, text file)
2016-01-31 Laser(UART)-Nucleo pinout, initial struggle
2016-02-05 Getting one clean reading from the laser.
2016-02-05 Getting multiple readings from the laser.
2016-02-05 Copied laser code
2016-02-05 Working laser w/function calls. Needs speedup.
2016-02-05 Finished laser
2016-02-06 sync (starting Code/main/)
2016-02-06 Begin work on F030 bareboard
2016-02-07 Sync - worked on bare MCU
2016-02-07 Clean up directories
2016-02-07 Add Ross' schematic
2016-02-07 Add PinoutMinimal (done)
2016-02-08 Add STM32L476RET schematic, clean-up folders
2016-02-08 Work on minimal schematic, add power components
2016-02-09 Add schematic for the power subsystem, create all missing components
2016-02-11 Add Digikey invoices
2016-02-12 Add images used in the presentation
2016-02-12 Add presentation images, finish draft
2016-02-13 Add Codec, Bluetooth, debug to minimal schematic
2016-02-17 Add schematic (schematic done, need to draw footprints and design PCB layout)
2016-02-17 Add push buttons and battery switch to schematic
2016-02-17 Add HW footprints info, minor schematic change (mic)
2016-02-18 Update schematic (add software audio capability, prettier)
2016-02-18 Rename folder: schema->pdf
2016-02-19 sync (minor schematic change)
2016-02-19 Assign some footprints to schematic
2016-02-20 Update schematic, change compass (LGA->QFN)
2016-02-20 Update schematic, order capacitors/resistors/headers and list their size in HW
2016-02-21 Finish schematic, finish drawing footprints, associate all parts to footprints, get a reading from the GPS.
2016-02-22 Working on the PCB (third attempt). Misc schematic fixes (charger always on)
2016-02-22 Slight progress on PCB attempt 3
2016-02-23 PCB3 progress: Needs capacitors/resistors and push buttons
2016-02-23 Progressing on the PCB. Completed pinout for the standard board.
2016-02-23 Organize folders
2016-02-24 Working on PCB#4, now with FreeRouting
2016-02-25 Lots of progress on the mPCB
2016-02-26 PCB4-23
2016-02-26 PCB4:25
2016-02-26 PCB svg render
2016-02-29 Ordered PCB. Making no progress on the compass.
2016-02-29 Bedsync. Compass: applied a NSS/CS fix found on a forum, still no progress.
2016-02-29 Update standard board pinout
2016-03-04 Compass (desperate times): crap is about to get deleted
2016-03-04 Compass: killing it.
2016-03-09 sync (compass data)
2016-03-09 sync: trying to translate the magnet readings
2016-03-19 Compass works, pulling valid data.
2016-03-21 Compass appears to be flawless
2016-04-08 SW9000 on IAR
2016-04-13 Merging the things (Desktop)
2016-04-16 Laser cutter cad file for Sensewalk 9000
2016-04-16 Sensewalk 9000 development, worked on the GPS with Diego
2016-04-16 Sensewalk 9000 development (vibrator, laser, sd), worked on GPS with Diego
2016-04-17 Started work on compass w/ vibration and interrupt, starting STM32F7 board
2016-04-17 sync, SW9000->SW2
2016-04-19 Add presentation and Ross' board
2016-04-22 Code that was presented
2016-04-27 GPS: About to remove RTOS
2016-04-29 Fixed GPS code for Diego to graduate
2016-04-29 Organize files
2016-04-30 Modify final paper
2016-05-02 Add final documentation
